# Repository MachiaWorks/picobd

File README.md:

# picobd
30% (close to 40%) keyboard using Raspberry Pi Pico.
Picobd is an abbreviation of "Raspberry pi pico keyboard".

detail:

https://machiaworx.net/?p=1359
 
# Warning(important)

If you place an order or build a keyboard using these sets of files, please use them at your own risk.
Even if damage occurs during construction, the author will not take any responsibility. 

# build 

## manufacturing PCB/Plates

use "pcb.zip","plate.zip",and "bottom.zip" in "/gerber".

I usually order from JLCPCB in manufacturing.

## required parts

* Raspberry Pi Pico
* Keyswitch * 38
* Keycap * 38
* M2 8mm Screw * 10
* M2 3mm Screw * 10
* M2 3mm spacer * 10
* M2 5mm spacer * 10
* gom ashi
* USB micro cable

## build guide

under construction...

## using firmware(under construction.)

PRK firmware

https://github.com/picoruby/prk_firmware

http://www.keyboard-layout-editor.com/##@@=q&=w&=e&=r&=t&_x:0.5&c=%23eb8da9&w:1.25&h:3%3B&=raspi%20pico&_c=%23cccccc%3B&=y&=u&=i&=o&_w:1.25%3B&=p%3B&@_w:1.25%3B&=a&=s&=d&=f&=g&_x:1.75%3B&=h&=j&=k&=l&=shift%3B&@_w:1.5%3B&=z%2F%2Fshift&=x&=c&=v&=b&_x:1.75%3B&=n&=m&=up&_w:1.75%3B&=enter%3B&@_x:0.25&w:1.25%3B&=os&_w:1.25%3B&=alt&_w:1.25%3B&=ctrl&_w:1.75%3B&=spc&_w:1.75%3B&=spc&_w:1.25%3B&=ctrl&=left&=down&=right/

KMK firmware

under construction...

# design(Thanks to each tool and library author)

## using layout designing

Keyboard Layout Editor

http://www.keyboard-layout-editor.com/

Plate & Case Builder

http://builder.swillkb.com/

##  using KiCAD library

KBD - for building keyboard libraries

https://github.com/foostan/kbd

su120-keyboard

https://github.com/e3w2q/su120-keyboard

KiCad-RP-Pico

https://github.com/ncarandini/KiCad-RP-Pico

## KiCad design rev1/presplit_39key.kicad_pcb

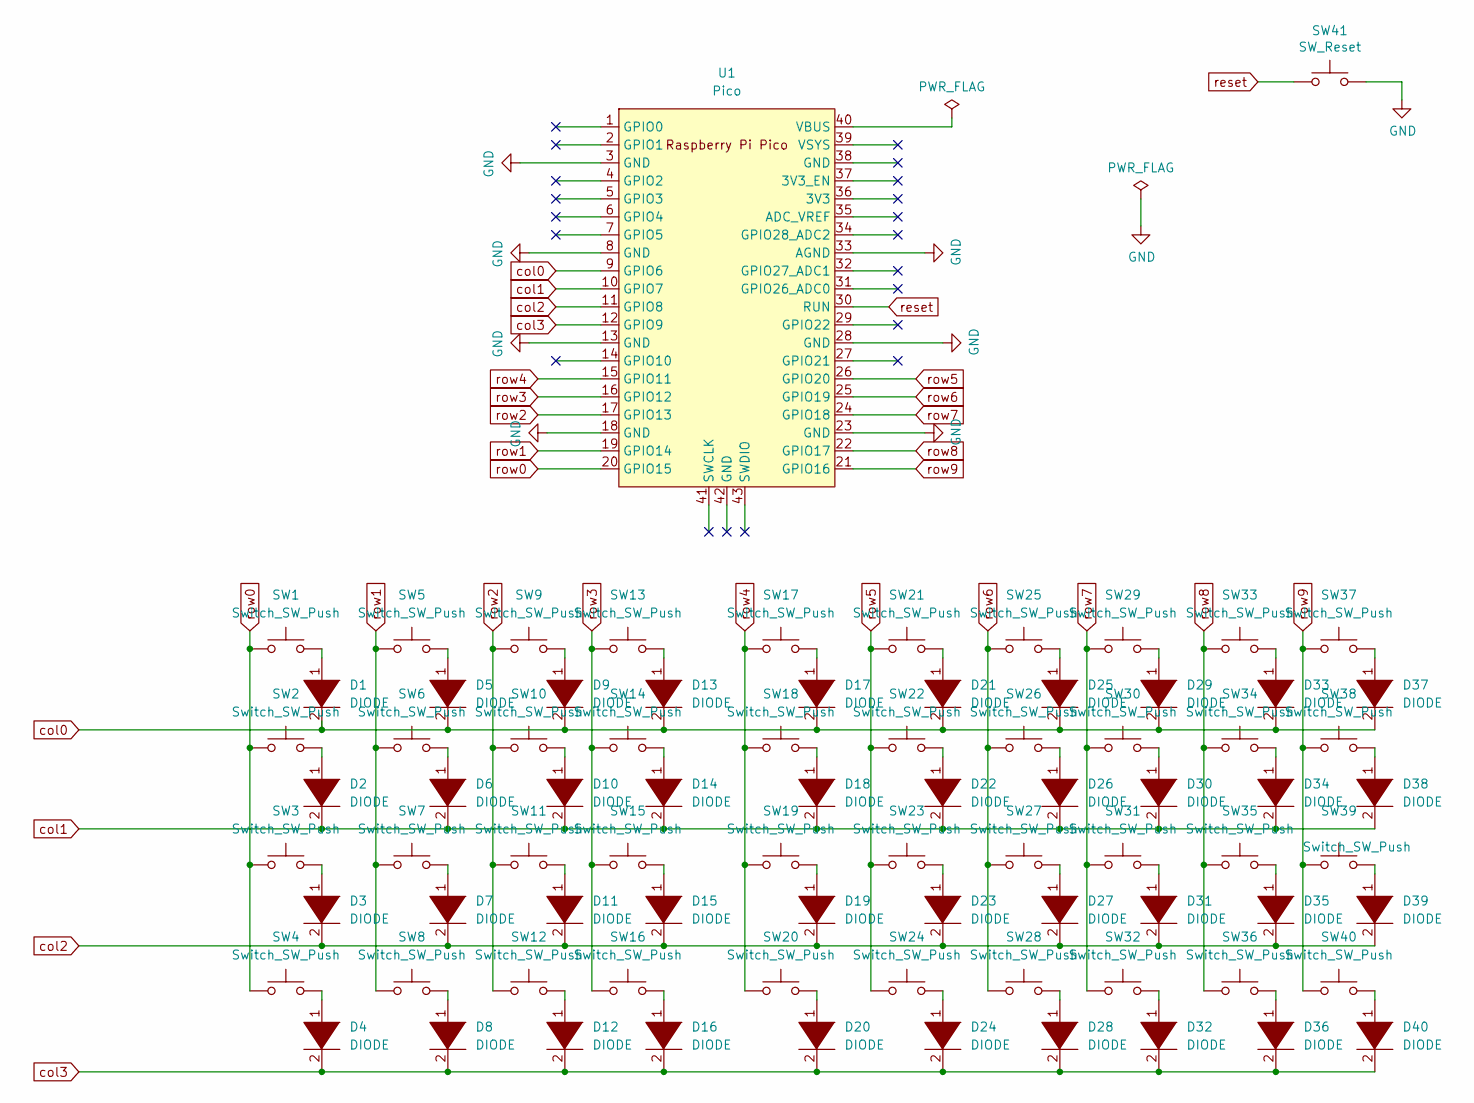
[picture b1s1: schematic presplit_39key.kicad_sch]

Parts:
D1, D2, D3, D4, D5, D6, D7, D8, D9, D10, D11, D12, D13, D14, D15, D16, D17, D18, D19, D20, D21, D22, D23, D24, D25, D26, D27, D28, D29, D30, D31, D32, D33, D34, D35, D36, D37, D38, D39, D40: DIODE; D3_TH_SMD_v2
SW1, SW2, SW3, SW4, SW5, SW6, SW7, SW8, SW9, SW10, SW11, SW12, SW13, SW14, SW15, SW16, SW17, SW18, SW19, SW20, SW21, SW22, SW23, SW24, SW25, SW26, SW27, SW28, SW29, SW30, SW31, SW32, SW33, SW34, SW35, SW36, SW37, SW38, SW39, SW40: Switch_SW_Push; CherryMX_1u
SW41: SW_Reset; ResetSW
U1: Pico; RPi_Pico_SMD_TH

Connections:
GND: SW41.2, U1.3 (GND), U1.8 (GND), U1.13 (GND), U1.18 (GND), U1.23 (GND), U1.28 (GND), U1.33 (AGND)
unnamed: D1.1 (K), SW1.2
unnamed: D2.1 (K), SW2.2
unnamed: D3.1 (K), SW3.2
unnamed: D4.1 (K), SW4.2
unnamed: D5.1 (K), SW5.2
unnamed: D6.1 (K), SW6.2
unnamed: D7.1 (K), SW7.2
unnamed: D8.1 (K), SW8.2
unnamed: D9.1 (K), SW9.2
unnamed: D10.1 (K), SW10.2
unnamed: D11.1 (K), SW11.2
unnamed: D12.1 (K), SW12.2
unnamed: D13.1 (K), SW13.2
unnamed: D14.1 (K), SW14.2
unnamed: D15.1 (K), SW15.2
unnamed: D16.1 (K), SW16.2
unnamed: D17.1 (K), SW17.2
unnamed: D18.1 (K), SW18.2
unnamed: D19.1 (K), SW19.2
unnamed: D20.1 (K), SW20.2
unnamed: D21.1 (K), SW21.2
unnamed: D22.1 (K), SW22.2
unnamed: D23.1 (K), SW23.2
unnamed: D24.1 (K), SW24.2
unnamed: D25.1 (K), SW25.2
unnamed: D26.1 (K), SW26.2
unnamed: D27.1 (K), SW27.2
unnamed: D28.1 (K), SW28.2
unnamed: D29.1 (K), SW29.2
unnamed: D30.1 (K), SW30.2
unnamed: D31.1 (K), SW31.2
unnamed: D32.1 (K), SW32.2
unnamed: D33.1 (K), SW33.2
unnamed: D34.1 (K), SW34.2
unnamed: D35.1 (K), SW35.2
unnamed: D36.1 (K), SW36.2
unnamed: D37.1 (K), SW37.2
unnamed: D38.1 (K), SW38.2
unnamed: D39.1 (K), SW39.2
unnamed: D40.1 (K), SW40.2
col0: D1.2 (A), D5.2 (A), D9.2 (A), D13.2 (A), D17.2 (A), D21.2 (A), D25.2 (A), D29.2 (A), D33.2 (A), D37.2 (A), U1.9 (GPIO6)
col1: D2.2 (A), D6.2 (A), D10.2 (A), D14.2 (A), D18.2 (A), D22.2 (A), D26.2 (A), D30.2 (A), D34.2 (A), D38.2 (A), U1.10 (GPIO7)
col2: D3.2 (A), D7.2 (A), D11.2 (A), D15.2 (A), D19.2 (A), D23.2 (A), D27.2 (A), D31.2 (A), D35.2 (A), D39.2 (A), U1.11 (GPIO8)
col3: D4.2 (A), D8.2 (A), D12.2 (A), D16.2 (A), D20.2 (A), D24.2 (A), D28.2 (A), D32.2 (A), D36.2 (A), D40.2 (A), U1.12 (GPIO9)
reset: SW41.1, U1.30 (RUN)
row0: SW1.1, SW2.1, SW3.1, SW4.1, U1.20 (GPIO15)
row1: SW5.1, SW6.1, SW7.1, SW8.1, U1.19 (GPIO14)
row2: SW9.1, SW10.1, SW11.1, SW12.1, U1.17 (GPIO13)
row3: SW13.1, SW14.1, SW15.1, SW16.1, U1.16 (GPIO12)
row4: SW17.1, SW18.1, SW19.1, SW20.1, U1.15 (GPIO11)
row5: SW21.1, SW22.1, SW23.1, SW24.1, U1.26 (GPIO20)
row6: SW25.1, SW26.1, SW27.1, SW28.1, U1.25 (GPIO19)
row7: SW29.1, SW30.1, SW31.1, SW32.1, U1.24 (GPIO18)
row8: SW33.1, SW34.1, SW35.1, SW36.1, U1.22 (GPIO17)
row9: SW37.1, SW38.1, SW39.1, SW40.1, U1.21 (GPIO16)

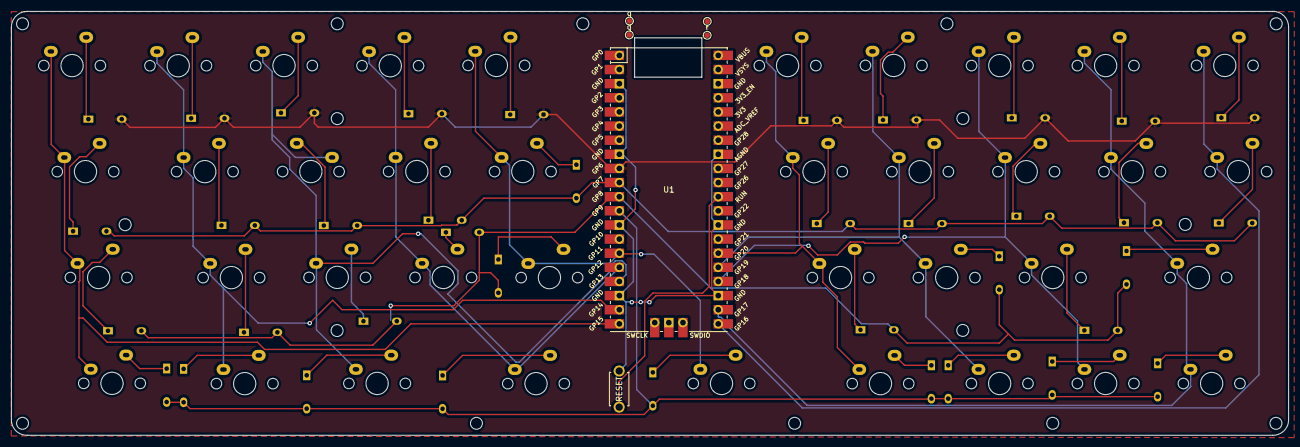
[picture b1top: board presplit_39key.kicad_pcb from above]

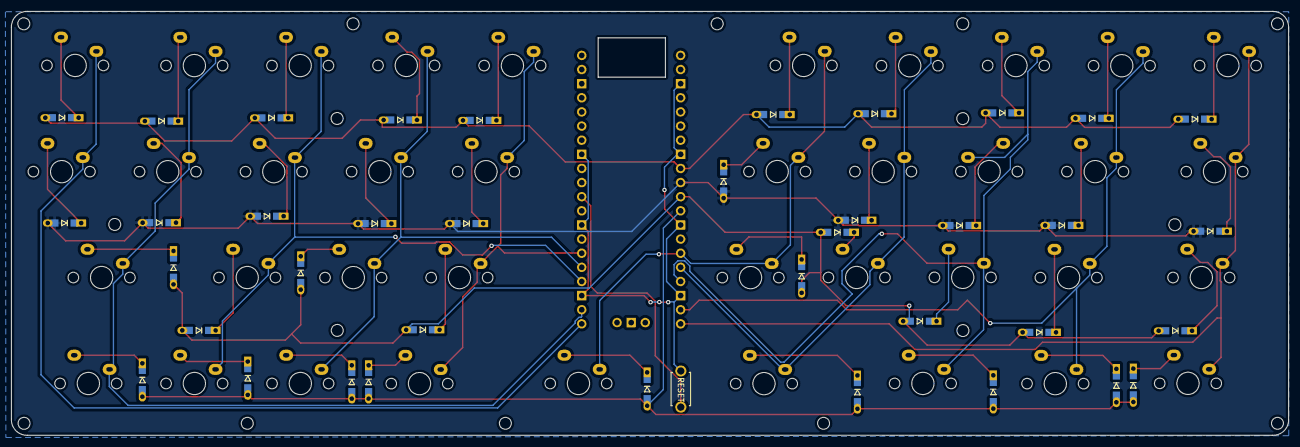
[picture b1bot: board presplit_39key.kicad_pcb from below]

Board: 2 copper layers, 229.6 x 76.2 mm, 81 parts (39 on the bottom side), 54 nets.

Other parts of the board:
q: TestPoint_Pad_D1.0mm
q#2: TestPoint_Pad_D1.0mm
r: TestPoint_Pad_D1.0mm

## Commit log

2022-03-18 initial commit(data pickup)
2022-03-18 data remove
2022-03-18 prk firmware data create
2022-03-18 warning added.
2022-03-18 Fixed embarrassing spelling mistakes
2022-03-18 layout data added
2022-03-20 update.
2022-03-27 Update(3layer use )
2022-03-27 added composition key/ hold key.
2022-03-27 fix composite/mode key.
2022-03-27 make keyboard layout link
2022-04-02 folder moved.
